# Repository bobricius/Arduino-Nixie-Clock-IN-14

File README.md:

Features:

- 24h mode
- easy assembly
- arduino compatible firmware ATMEGA328 or another runing on internal RC oscillator (no crystal needed )
- ultra high precise time with RTC DS3231 onboard or RTC module
- CR2032 battery backup
- separated HV power supply (not included, you can connect any HV module) 
 etc. specially THIS ONE from ebay fit prefect.
- beautiful white single board 
- readable clean design
- cathode poisoning prevention
- 3mm holes under nixies for optional back-light
- optional DS18B20 sensor
- dimensions 15cm x 10cm

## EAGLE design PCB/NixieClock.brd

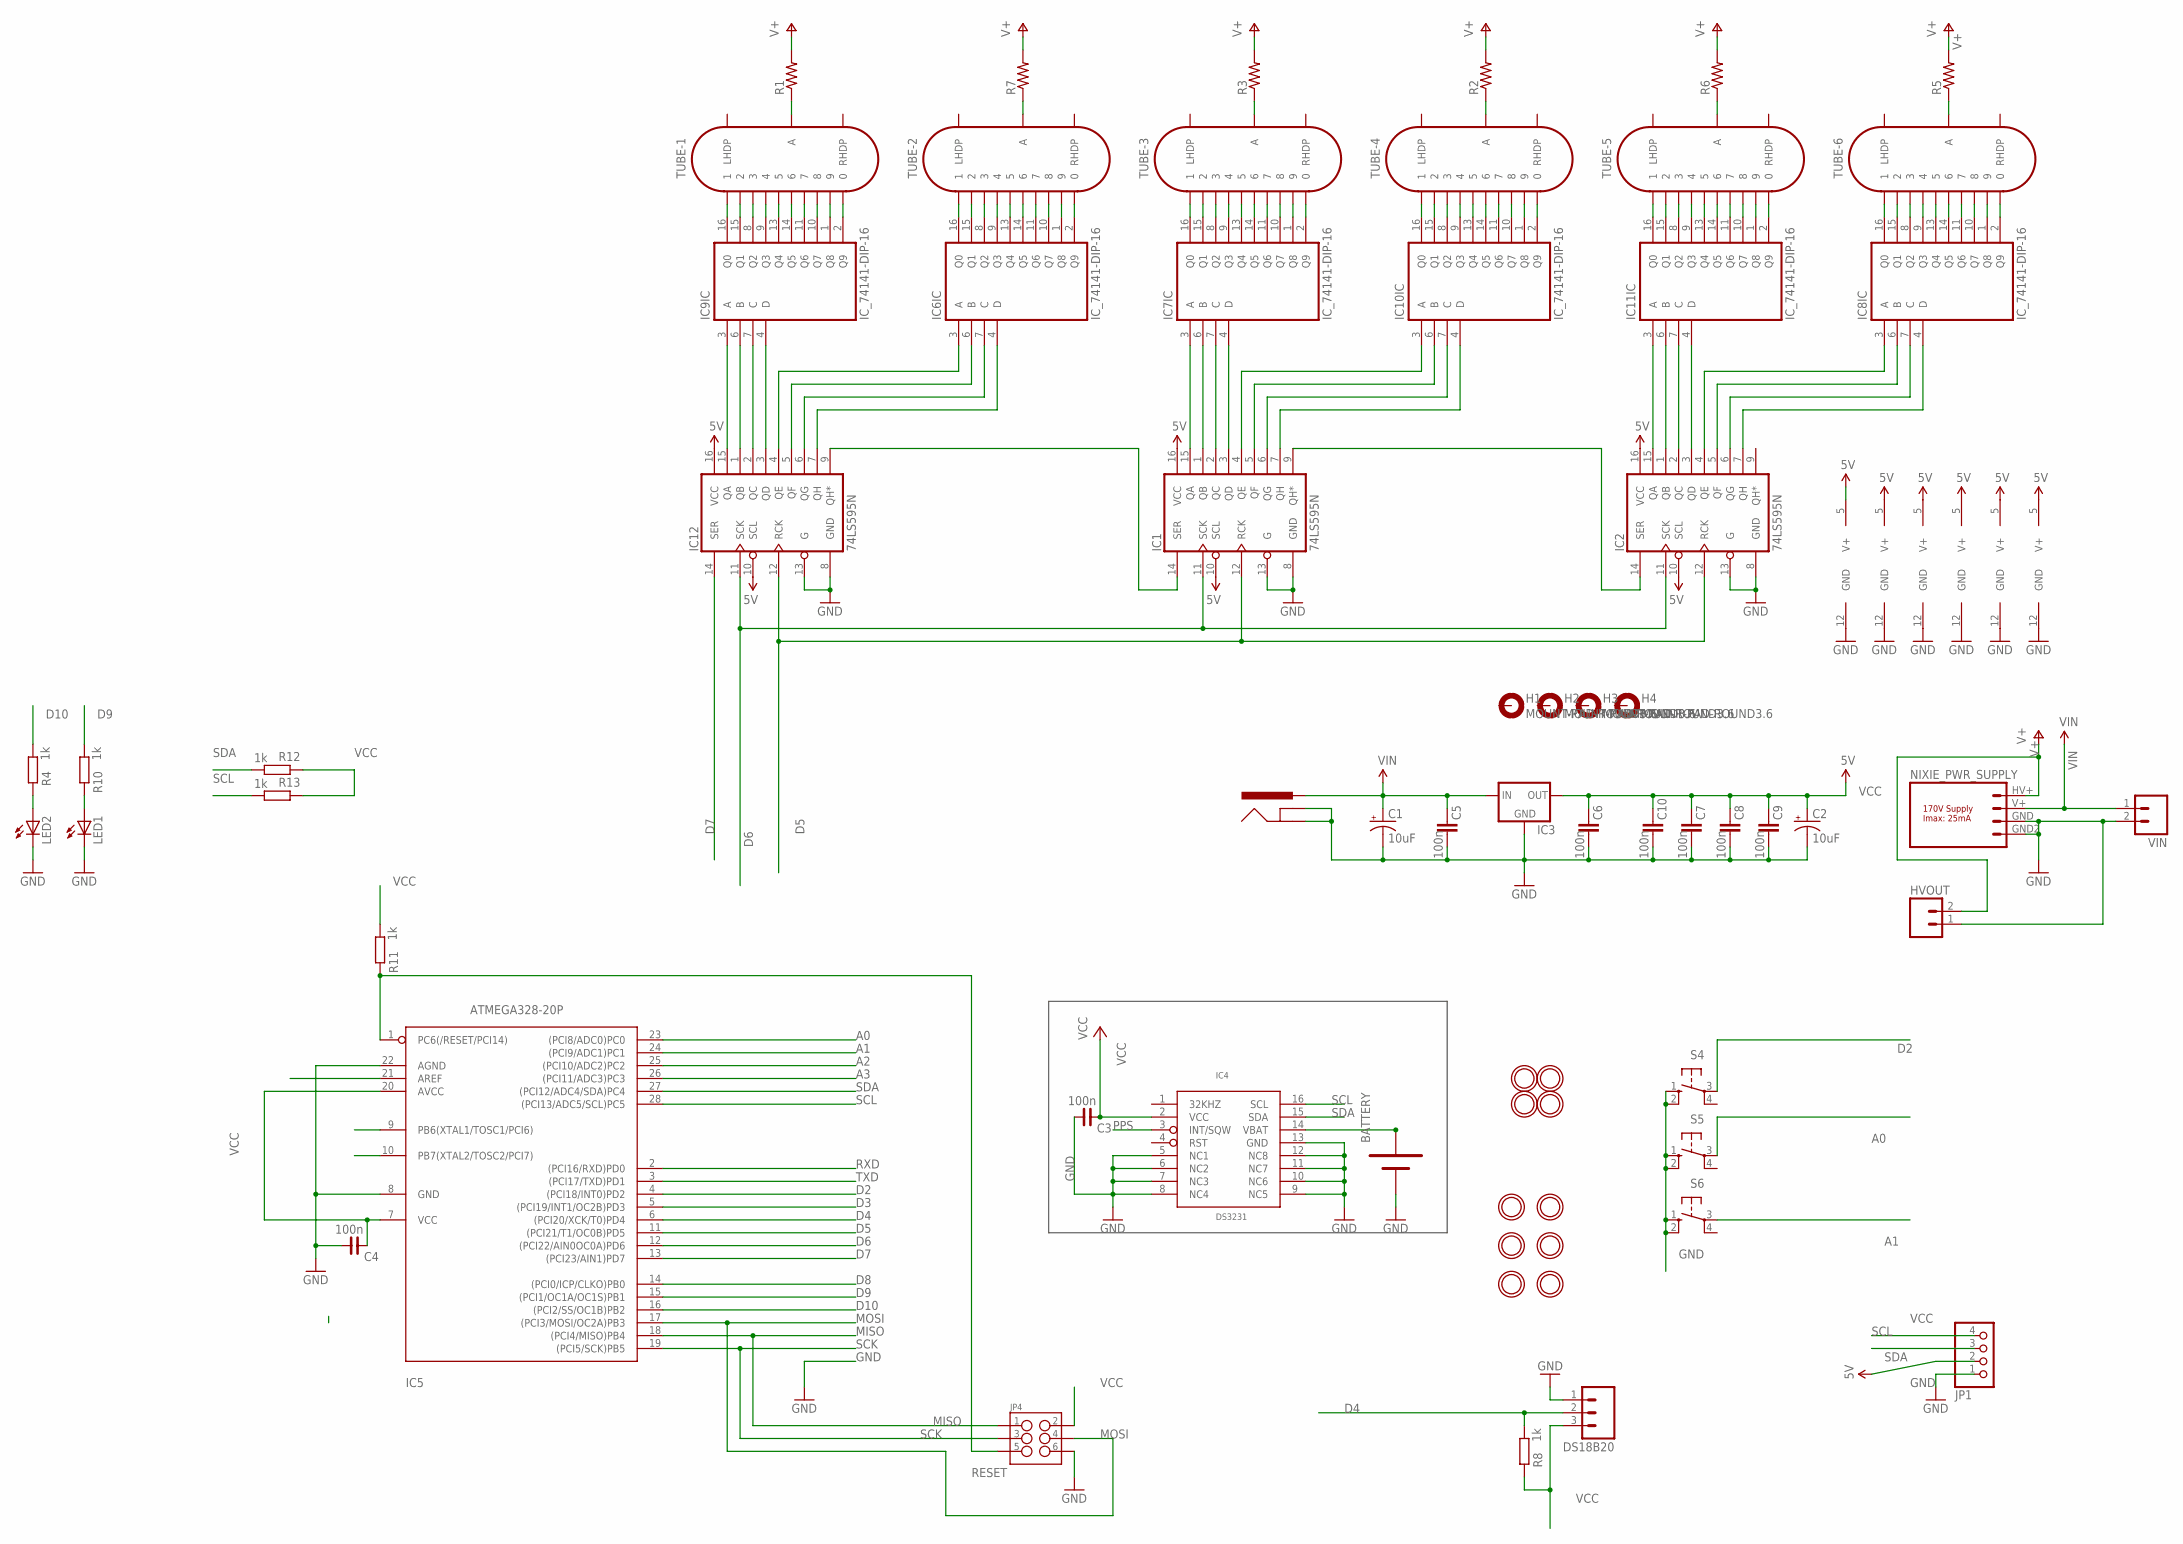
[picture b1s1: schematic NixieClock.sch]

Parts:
BATTERY: BATTERY-1XAA20MM; BATTCOM_20MM_PTH
C1, C2: 10uF; CPOL-RADIAL-10UF-25V
C3, C4: 100n; C0603
C5, C6, C7, C8, C9, C10: 100n; C050-025X075
DS18B20: DS18B20DS18B20; DS18B20
H1, H2, H3, H4: MOUNT-PAD-ROUND3.6; 3,6-PAD
HVOUT: M02PTH; 1X02
IC1, IC2, IC12: 74LS595N; DIL16
IC3: V_REG_78XXSIDE; 78XXL
IC4: DS3231; SO16W
IC5: ATMEGA328-20P; DIL28-3
IC6, IC7, IC8, IC9, IC10, IC11: IC_74141-DIP-16; DIL16
J1: POWER_JACKPTH; POWER_JACK_PTH
JP1: PINHD-1X4; 1X04
JP4: M03X2NO_SILK; 2X3-NS
LED1, LED2: LED3MM
NIXIE_PWR_SUPPLY: NIXIE_PWR_SUPPLYPTH; NIXIE_PWR_SUPPLY
R1, R2, R3, R5, R6, R7: RESISTORPTH-1/4W; AXIAL-0.4
R4, R8, R10, R11, R12, R13: 1k; 0204/5
S4, S5, S6: 10-XX; B3F-10XX
TUBE-1, TUBE-2, TUBE-3, TUBE-4, TUBE-5, TUBE-6: IN-14
U$10, U$11, U$16, U$17, U$18, U$19, U$21, U$22, U$23, U$24: MOUNTINGHOLE3.0THIN; MOUNTINGHOLE_3.0_PLATEDTHIN
VIN: M02PTH; 1X02

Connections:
A0: IC5.23 ((PCI8/ADC0)PC0), S5.3
A1: IC5.24 ((PCI9/ADC1)PC1), S6.3
A2: IC5.25 ((PCI10/ADC2)PC2)
A3: IC5.26 ((PCI11/ADC3)PC3)
AREF_RAW: IC5.21 (AREF)
D2: IC5.4 ((PCI18/INT0)PD2), S4.3
D3: IC5.5 ((PCI19/INT1/OC2B)PD3)
D4: DS18B20.2 (DS), IC5.6 ((PCI20/XCK/T0)PD4), R8.1
D5: IC1.12 (RCK), IC2.12 (RCK), IC5.11 ((PCI21/T1/OC0B)PD5), IC12.12 (RCK)
D6: IC1.11 (SCK), IC2.11 (SCK), IC5.12 ((PCI22/AIN0OC0A)PD6), IC12.11 (SCK)
D7: IC5.13 ((PCI23/AIN1)PD7), IC12.14 (SER)
D8: IC5.14 ((PCI0/ICP/CLKO)PB0)
D9: IC5.15 ((PCI1/OC1A/OC1S)PB1), R10.1
D10: IC5.16 ((PCI2/SS/OC1B)PB2), R4.1
GND: BATTERY.-, C1.2 (-), C2.2 (-), C3.1, C4.1, C5.2, C6.2, C7.2, C8.2, C9.2, C10.2, DS18B20.1 (GND), HVOUT.1, IC1.8 (GND), IC1.13 (G), IC2.8 (GND), IC2.13 (G), IC3.GND, IC4.5 (NC1), IC4.6 (NC2), IC4.7 (NC3), IC4.8 (NC4), IC4.9 (NC5), IC4.10 (NC6), IC4.11 (NC7), IC4.12 (NC8), IC4.13 (GND), IC5.8 (GND), IC5.22 (AGND), IC6.12 (GND), IC7.12 (GND), IC8.12 (GND), IC9.12 (GND), IC10.12 (GND), IC11.12 (GND), IC12.8 (GND), IC12.13 (G), J1.GND, J1.GNDBREAK, JP1.1, JP4.6, LED1.K (C), LED2.K (C), NIXIE_PWR_SUPPLY.GND (4), NIXIE_PWR_SUPPLY.GND2 (1), S4.1 (S), S4.2 (S1), S5.1 (S), S5.2 (S1), S6.1 (S), S6.2 (S1), VIN.2
MISO: IC5.18 ((PCI4/MISO)PB4), JP4.1
MOSI: IC5.17 ((PCI3/MOSI/OC2A)PB3), JP4.4
unnamed: R1.P$1 (1), TUBE-1.A
unnamed: R7.P$1 (1), TUBE-2.A
unnamed: R3.P$1 (1), TUBE-3.A
unnamed: R2.P$1 (1), TUBE-4.A
unnamed: R6.P$1 (1), TUBE-5.A
unnamed: R5.P$1 (1), TUBE-6.A
unnamed: IC9.16 (Q0), TUBE-1.1
unnamed: IC9.15 (Q1), TUBE-1.2
unnamed: IC9.8 (Q2), TUBE-1.3
unnamed: IC9.9 (Q3), TUBE-1.4
unnamed: IC9.13 (Q4), TUBE-1.5
unnamed: IC9.14 (Q5), TUBE-1.6
unnamed: IC9.11 (Q6), TUBE-1.7
unnamed: IC9.10 (Q7), TUBE-1.8
unnamed: IC9.1 (Q8), TUBE-1.9
unnamed: IC9.2 (Q9), TUBE-1.0
unnamed: IC6.16 (Q0), TUBE-2.1
unnamed: IC6.15 (Q1), TUBE-2.2
unnamed: IC6.8 (Q2), TUBE-2.3
unnamed: IC6.9 (Q3), TUBE-2.4
unnamed: IC6.13 (Q4), TUBE-2.5
unnamed: IC6.14 (Q5), TUBE-2.6
unnamed: IC6.11 (Q6), TUBE-2.7
unnamed: IC6.10 (Q7), TUBE-2.8
unnamed: IC6.1 (Q8), TUBE-2.9
unnamed: IC6.2 (Q9), TUBE-2.0
unnamed: IC7.16 (Q0), TUBE-3.1
unnamed: IC7.15 (Q1), TUBE-3.2
unnamed: IC7.8 (Q2), TUBE-3.3
unnamed: IC7.9 (Q3), TUBE-3.4
unnamed: IC7.13 (Q4), TUBE-3.5
unnamed: IC7.14 (Q5), TUBE-3.6
unnamed: IC7.11 (Q6), TUBE-3.7
unnamed: IC7.10 (Q7), TUBE-3.8
unnamed: IC7.1 (Q8), TUBE-3.9
unnamed: IC7.2 (Q9), TUBE-3.0
unnamed: IC10.16 (Q0), TUBE-4.1
unnamed: IC10.15 (Q1), TUBE-4.2
unnamed: IC10.8 (Q2), TUBE-4.3
unnamed: IC10.9 (Q3), TUBE-4.4
unnamed: IC10.13 (Q4), TUBE-4.5
unnamed: IC10.14 (Q5), TUBE-4.6
unnamed: IC10.11 (Q6), TUBE-4.7
unnamed: IC10.10 (Q7), TUBE-4.8
unnamed: IC10.1 (Q8), TUBE-4.9
unnamed: IC10.2 (Q9), TUBE-4.0
unnamed: IC11.16 (Q0), TUBE-5.1
unnamed: IC11.15 (Q1), TUBE-5.2
unnamed: IC11.8 (Q2), TUBE-5.3
unnamed: IC11.9 (Q3), TUBE-5.4
unnamed: IC11.13 (Q4), TUBE-5.5
unnamed: IC11.14 (Q5), TUBE-5.6
unnamed: IC11.11 (Q6), TUBE-5.7
unnamed: IC11.10 (Q7), TUBE-5.8
unnamed: IC11.1 (Q8), TUBE-5.9
unnamed: IC11.2 (Q9), TUBE-5.0
unnamed: IC8.16 (Q0), TUBE-6.1
unnamed: IC8.15 (Q1), TUBE-6.2
unnamed: IC8.8 (Q2), TUBE-6.3
unnamed: IC8.9 (Q3), TUBE-6.4
unnamed: IC8.13 (Q4), TUBE-6.5
unnamed: IC8.14 (Q5), TUBE-6.6
unnamed: IC8.11 (Q6), TUBE-6.7
unnamed: IC8.10 (Q7), TUBE-6.8
unnamed: IC8.1 (Q8), TUBE-6.9
unnamed: IC8.2 (Q9), TUBE-6.0
unnamed: IC1.1 (QB), IC7.6 (B)
unnamed: IC1.2 (QC), IC7.7 (C)
unnamed: IC1.3 (QD), IC7.4 (D)
unnamed: IC1.15 (QA), IC7.3 (A)
unnamed: IC9.6 (B), IC12.1 (QB)
unnamed: IC9.7 (C), IC12.2 (QC)
unnamed: IC9.4 (D), IC12.3 (QD)
unnamed: IC9.3 (A), IC12.15 (QA)
unnamed: IC2.1 (QB), IC11.6 (B)
unnamed: IC2.2 (QC), IC11.7 (C)
unnamed: IC2.3 (QD), IC11.4 (D)
unnamed: IC2.15 (QA), IC11.3 (A)
unnamed: IC6.3 (A), IC12.4 (QE)
unnamed: IC6.6 (B), IC12.5 (QF)
unnamed: IC6.7 (C), IC12.6 (QG)
unnamed: IC6.4 (D), IC12.7 (QH)
unnamed: IC1.14 (SER), IC12.9 (QH*)
unnamed: IC1.9 (QH*), IC2.14 (SER)
unnamed: IC1.4 (QE), IC10.3 (A)
unnamed: IC1.5 (QF), IC10.6 (B)
unnamed: IC1.6 (QG), IC10.7 (C)
unnamed: IC1.7 (QH), IC10.4 (D)
unnamed: LED2.A, R4.2
unnamed: IC2.4 (QE), IC8.3 (A)
unnamed: IC2.5 (QF), IC8.6 (B)
unnamed: IC2.6 (QG), IC8.7 (C)
unnamed: IC2.7 (QH), IC8.4 (D)
unnamed: BATTERY.+, IC4.14 (VBAT)
unnamed: LED1.A, R10.2
PPS: IC4.3 (INT/SQW)
RESET: IC5.1 (PC6(/RESET/PCI14)), JP4.5, R11.2
RXD: IC5.2 ((PCI16/RXD)PD0)
SCK: IC5.19 ((PCI5/SCK)PB5), JP4.3
SCL: IC4.16 (SCL), IC5.28 ((PCI13/ADC5/SCL)PC5), JP1.4, R13.1
SDA: IC4.15 (SDA), IC5.27 ((PCI12/ADC4/SDA)PC4), JP1.3, R12.1
TXD: IC5.3 ((PCI17/TXD)PD1)
V+: HVOUT.2, NIXIE_PWR_SUPPLY.HV+ (3), R1.P$2 (2), R2.P$2 (2), R3.P$2 (2), R5.P$2 (2), R6.P$2 (2), R7.P$2 (2)
VCC: C2.1 (+), C3.2, C4.2, C6.1, C7.1, C8.1, C9.1, C10.1, DS18B20.3 (5V), IC1.10 (SCL), IC1.16 (VCC), IC2.10 (SCL), IC2.16 (VCC), IC3.OUT, IC4.2 (VCC), IC5.7 (VCC), IC5.20 (AVCC), IC6.5 (V+), IC7.5 (V+), IC8.5 (V+), IC9.5 (V+), IC10.5 (V+), IC11.5 (V+), IC12.10 (SCL), IC12.16 (VCC), JP1.2, JP4.2, R8.2, R11.1, R12.2, R13.2
VIN: C1.1 (+), C5.1, IC3.IN, J1.PWR, NIXIE_PWR_SUPPLY.V+ (2), VIN.1

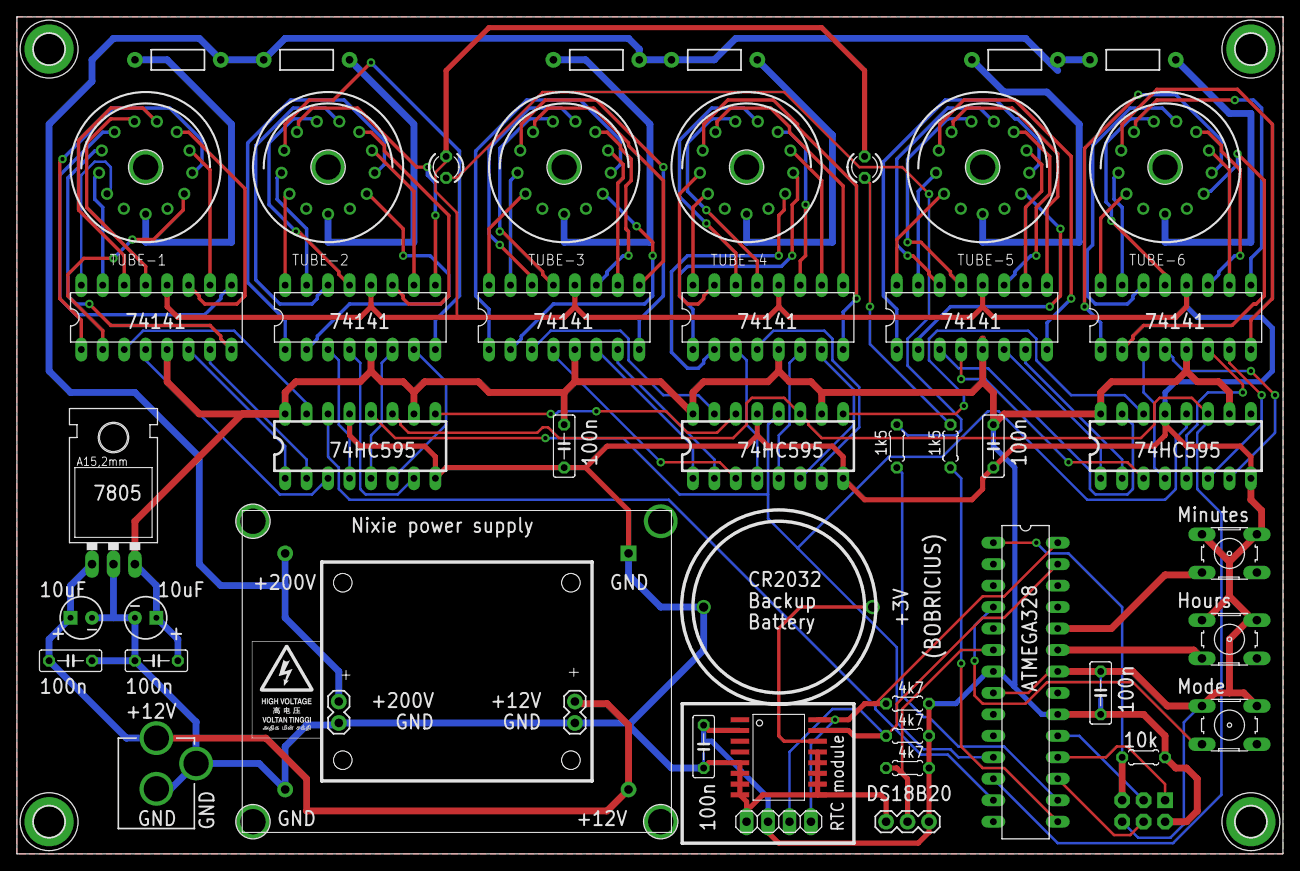
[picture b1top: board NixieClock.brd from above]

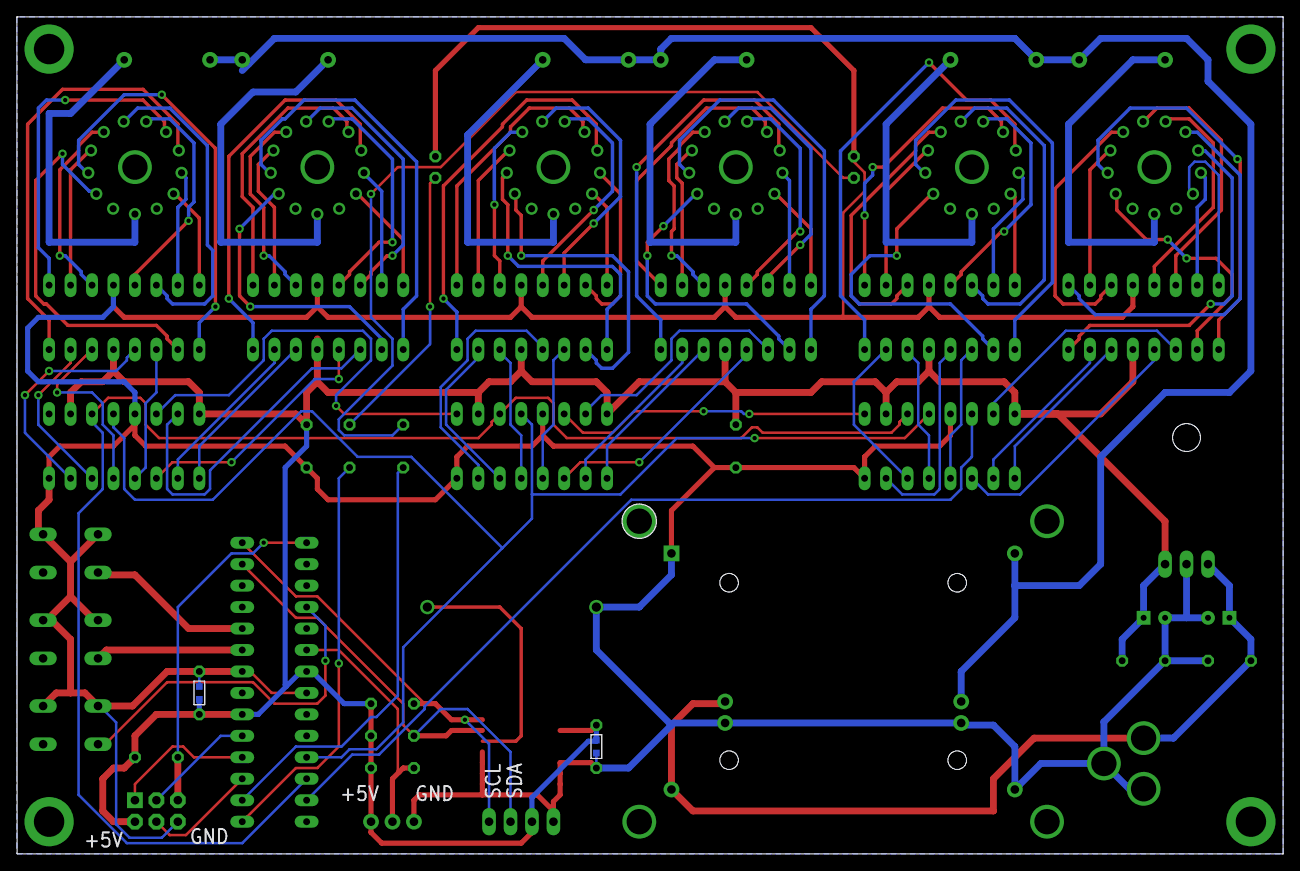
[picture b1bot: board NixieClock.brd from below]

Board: 2 copper layers, 149.9 x 99.1 mm, 68 parts (3 on the bottom side), 114 nets.

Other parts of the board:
U$20: HV03

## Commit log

2016-04-04 :neckbeard: Added .gitattributes & .gitignore files
2016-04-04 First upload
    Nixie clock PCB
2016-04-05 Update sketch

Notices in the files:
parts and their libraries:
SparkFun: Licensing: CC v3.0 Share-Alike You are welcome to use this library for commercial purposes.
